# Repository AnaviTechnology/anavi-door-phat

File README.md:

# Anavi Door pHAT

Anavi Door pHAT is an open source hardware Raspberry Pi pHAT (add-on board) for detecting if door is opened or closed. The board has been designed entirely with free and open source software. It features:

* Slots for up to 3 door sensors
* Piezoelectric buzzer
* Slot for PIR motion sensor
* Slots for up to 3 plug and play I2C sensors for temperature, barometric pressure, humidity and light
* UART (Universal asynchronous receiver/transmitter) pins for debugging
* EEPROM

# Dependencies

Uses PKM13EPYH4000-A0 footprint from https://github.com/nosuz/kicad-lib

# License

The project is released under the [Creative Commons Attribution-ShareAlike 4.0 International (CC BY-SA 4.0)](https://creativecommons.org/licenses/by-sa/4.0/).

Note: This is a human-readable summary of (and not a substitute for) the [license](https://creativecommons.org/licenses/by-sa/4.0/legalcode).

You are free to:

Share — copy and redistribute the material in any medium or format Adapt — remix, transform, and build upon the material for any purpose, even commercially. The licensor cannot revoke these freedoms as long as you follow the license terms. Under the following terms:

Attribution — You must give appropriate credit, provide a link to the license, and indicate if changes were made. You may do so in any reasonable manner, but not in any way that suggests the licensor endorses you or your use. ShareAlike — If you remix, transform, or build upon the material, you must distribute your contributions under the same license as the original. No additional restrictions — You may not apply legal terms or technological measures that legally restrict others from doing anything the license permits. Notices:

You do not have to comply with the license for elements of the material in the public domain or where your use is permitted by an applicable exception or limitation. No warranties are given. The license may not give you all of the permissions necessary for your intended use. For example, other rights such as publicity, privacy, or moral rights may limit how you use the material.

You will have to provide a link to the original creator of the project http://www.anavi.technology on any documentation or website.

Credit can be attributed through a link to the creator website: http://www.anavi.technology

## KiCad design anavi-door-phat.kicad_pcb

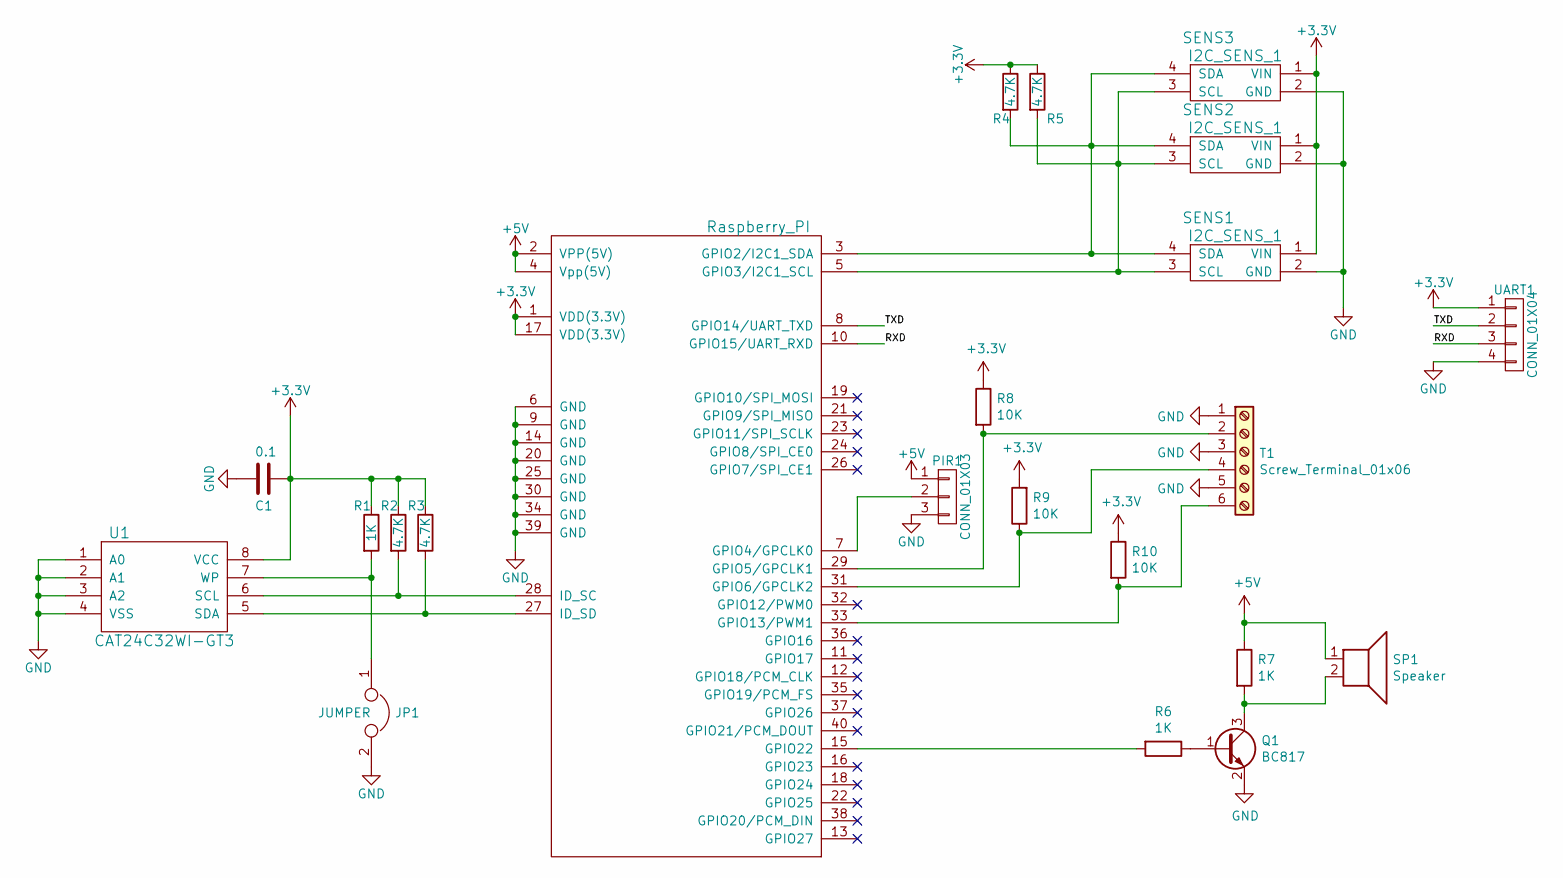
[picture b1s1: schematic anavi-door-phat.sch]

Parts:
C1: 0.1; C_0603_HandSoldering
JP1: JUMPER; Pin_Header_Straight_1x02
PIR1: CONN_01X03; Pin_Header_Straight_1x03
Q1: BC817; SOT-23
R1, R6, R7: 1K; R_0603_1608Metric
R2, R3, R4, R5: 4.7K; R_0603_1608Metric
R8, R9, R10: 10K; R_0603_1608Metric
RASP_CONN1: Raspberry_PI; Pin_Header_Straight_2x20
SENS1, SENS2, SENS3: I2C_SENS_1; Pin_Header_Straight_1x04
SP1: Speaker; PKM13EPYH4000-A0
T1: Screw_Terminal_01x06; TerminalBlock_Phoenix_MKDS-1,5-6_1x06_P5.00mm_Horizontal
U1: CAT24C32WI-GT3; DIP-8_W7.62mm
UART1: CONN_01X04; Pin_Header_Straight_1x04

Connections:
+3V3: C1.1, R1.1, R2.1, R3.1, R4.1, R5.1, R8.1, R9.2, R10.1, RASP_CONN1.1 (VDD(3.3V)), RASP_CONN1.17 (VDD(3.3V)), SENS1.1 (VIN), SENS2.1 (VIN), SENS3.1 (VIN), U1.8 (VCC), UART1.1; also elsewhere on the board
+5V: PIR1.1, R7.1, RASP_CONN1.2 (VPP(5V)), RASP_CONN1.4 (Vpp(5V)), SP1.1; also elsewhere on the board
/RXD: RASP_CONN1.10 (GPIO15/UART_RXD), UART1.3; also elsewhere on the board
/TXD: RASP_CONN1.8 (GPIO14/UART_TXD), UART1.2; also elsewhere on the board
GND: C1.2, JP1.2, PIR1.3, Q1.2 (E), RASP_CONN1.6 (GND), RASP_CONN1.9 (GND), RASP_CONN1.14 (GND), RASP_CONN1.20 (GND), RASP_CONN1.25 (GND), RASP_CONN1.30 (GND), RASP_CONN1.34 (GND), RASP_CONN1.39 (GND), SENS1.2 (GND), SENS2.2 (GND), SENS3.2 (GND), T1.1, T1.3, T1.5, U1.1 (A0), U1.2 (A1), U1.3 (A2), U1.4 (VSS), UART1.4; also elsewhere on the board
unnamed: JP1.1, R1.2, U1.7 (WP)
unnamed 6: PIR1.2, RASP_CONN1.7 (GPIO4/GPCLK0); also elsewhere on the board
unnamed: Q1.1 (B), R6.1
unnamed: Q1.3 (C), R7.2, SP1.2
unnamed: R2.2, RASP_CONN1.28 (ID_SC), U1.6 (SCL)
unnamed: R3.2, RASP_CONN1.27 (ID_SD), U1.5 (SDA)
unnamed: R4.2, RASP_CONN1.3 (GPIO2/I2C1_SDA), SENS1.4 (SDA), SENS2.4 (SDA), SENS3.4 (SDA)
unnamed: R5.2, RASP_CONN1.5 (GPIO3/I2C1_SCL), SENS1.3 (SCL), SENS2.3 (SCL), SENS3.3 (SCL)
unnamed: R6.2, RASP_CONN1.15 (GPIO22)
unnamed: R8.2, RASP_CONN1.29 (GPIO5/GPCLK1), T1.2
unnamed: R9.1, RASP_CONN1.31 (GPIO6/GPCLK2), T1.4
unnamed: R10.2, RASP_CONN1.33 (GPIO13/PWM1), T1.6

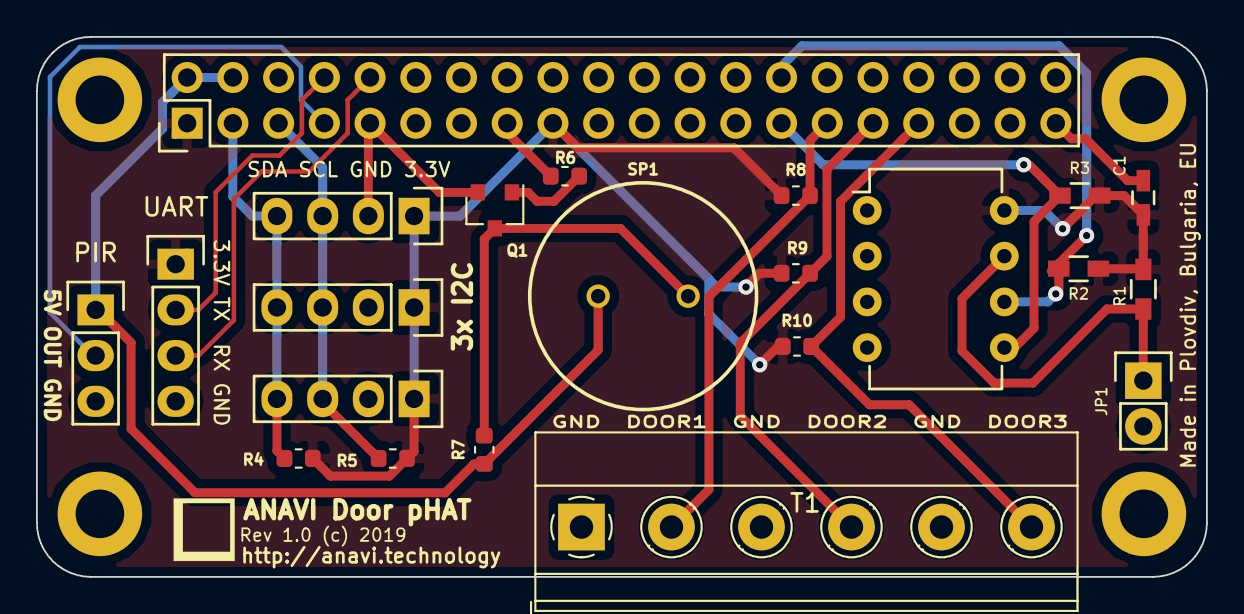
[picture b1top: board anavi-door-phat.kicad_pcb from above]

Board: 2 copper layers, 65.0 x 30.0 mm, 26 parts (0 on the bottom side), 17 nets.

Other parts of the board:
PIR: CONN_01X03; Pin_Header_Straight_1x03
REF1, REF2, REF3, REF4: MountingHole_2.7mm_M2.5_DIN965_Pad
UART: CONN_01X04; Pin_Header_Straight_1x04

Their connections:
+3V3: UART.1; also elsewhere on the board
+5V: PIR.1; also elsewhere on the board
/RXD: UART.3; also elsewhere on the board
/TXD: UART.2; also elsewhere on the board
GND: PIR.3, UART.4; also elsewhere on the board
unnamed 6: PIR.2; also elsewhere on the board

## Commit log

2019-02-20 anavi-door-phat: Initial release
    KiCad project for the open source hardware ANAVI Door pHAT.
2019-02-20 anavi-door-phat.kicad_pcb: Fix silkscreen
    Improve positions of the text on the silkscreen layer.
2019-03-19 anavi-door-phat.kicad_pcb: Assembly instructions
    Add notes for assembly on the F.Fab layer.

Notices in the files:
anavi-door-phat.kicad_pcb:
Rev 1.0 (c) 2019
